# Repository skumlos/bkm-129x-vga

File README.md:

The BKM-129X compatible with VGA instead of BNC.

Including a sync combiner circuit to run with both CSYNC and HVSYNC. This circuit was made up
by Ste from HD Retrovision as far as I know.

Requires Arduino Nano v3.0 loaded with the software from https://github.com/skumlos/bkm-129x-mcu

Revision log:

B: Fixed THS7374 bypass and VGA pin 9 connectivity. Update to Kicad 5.

A: Initial revision

(2020) Martin Hejnfelt (martin@hejnfelt.com)

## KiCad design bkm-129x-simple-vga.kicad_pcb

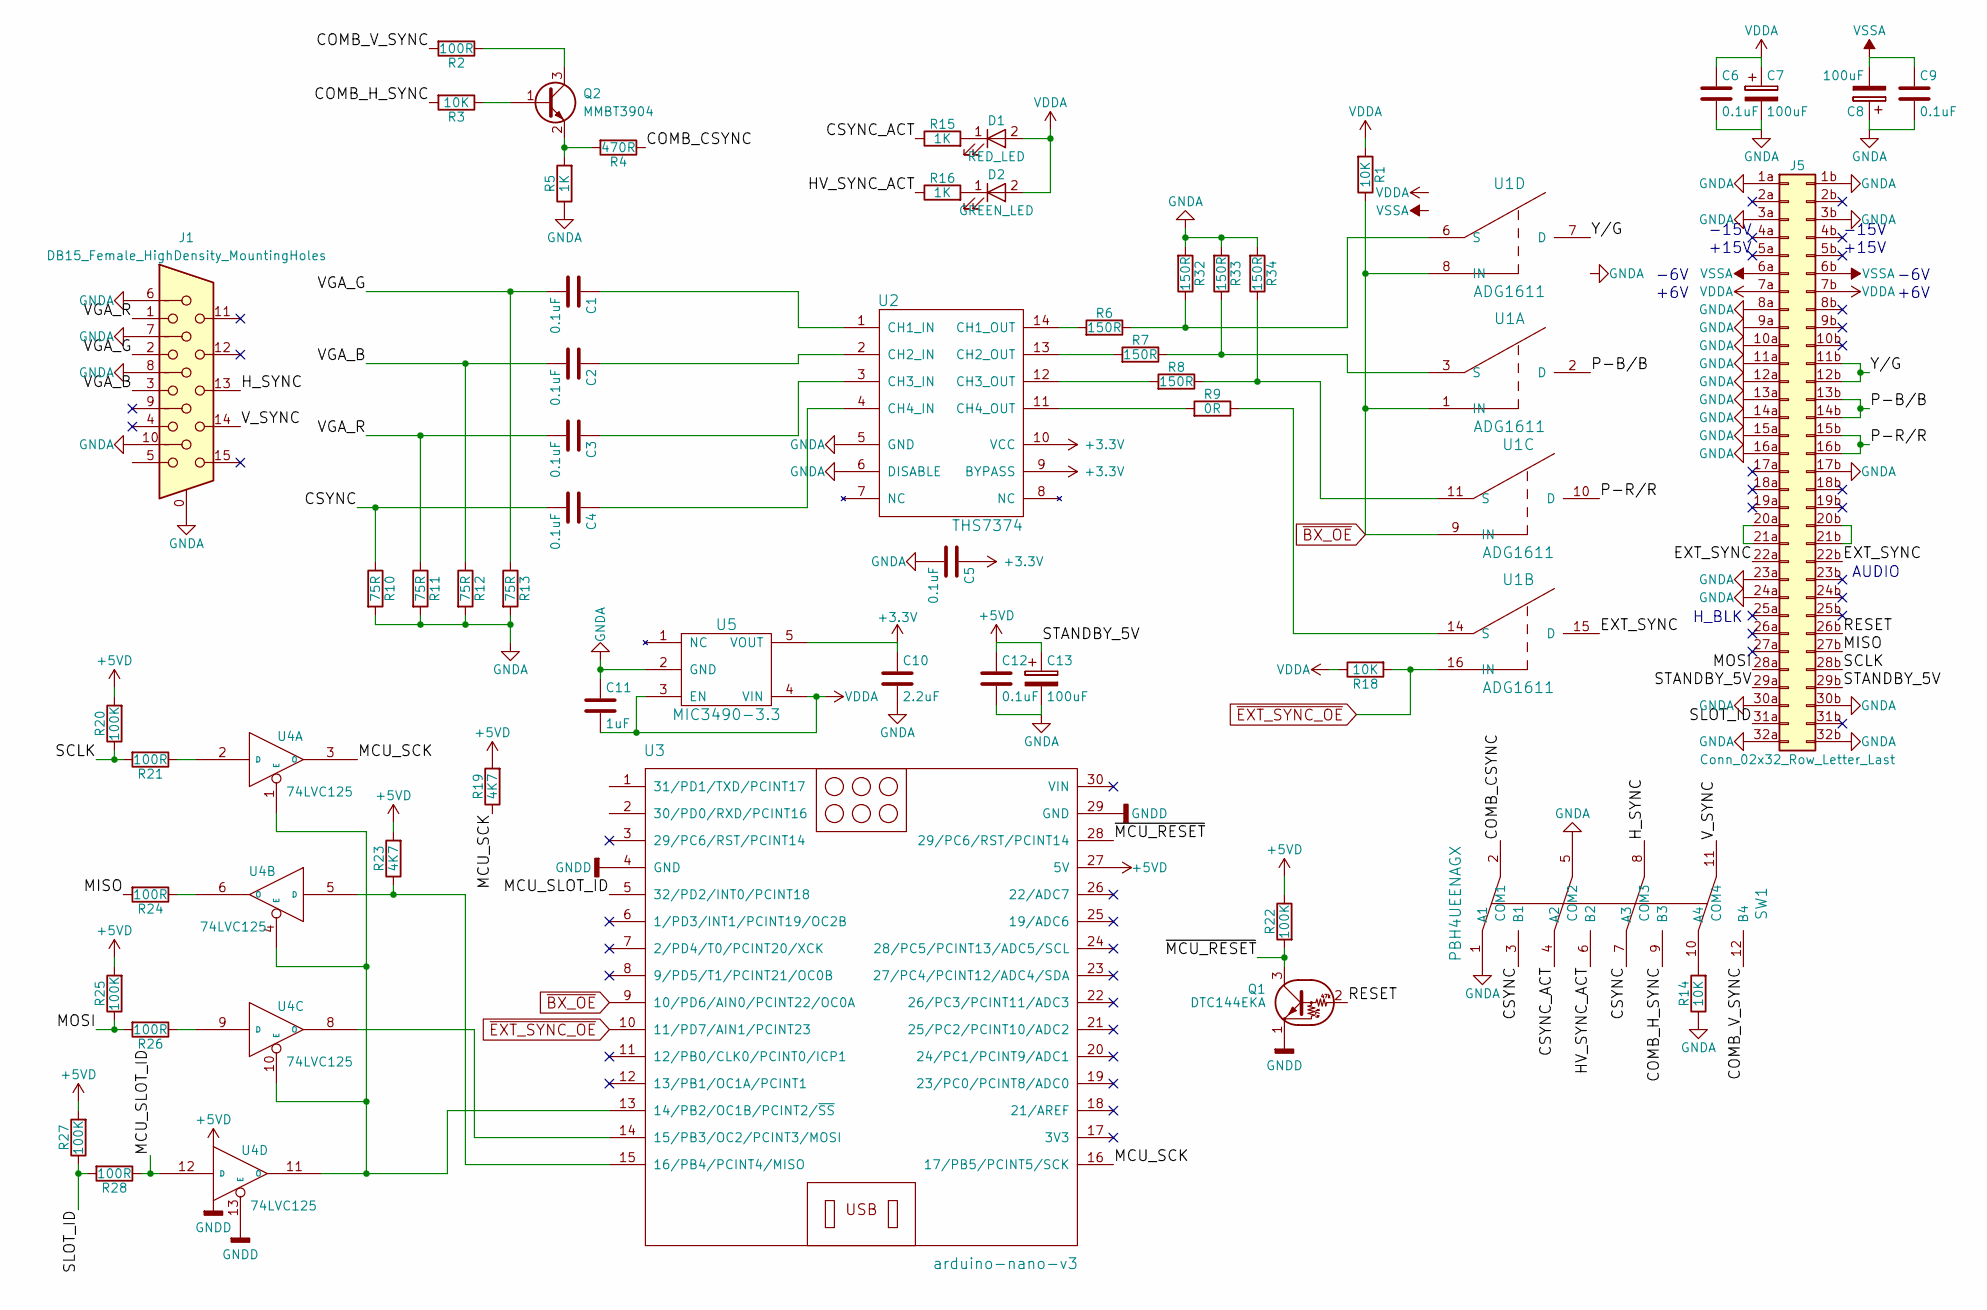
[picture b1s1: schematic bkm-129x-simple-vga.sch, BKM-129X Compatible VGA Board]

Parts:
C1, C2, C3, C4, C5, C6, C9, C12: 0.1uF; C_0805_HandSoldering
C7, C8, C13: 100uF; CP_Elec_6.3x5.3
C10: 2.2uF; C_0805_HandSoldering
C11: 1uF; C_0805_HandSoldering
D1: RED_LED; D_0805
D2: GREEN_LED; D_0805
J1: DB15_Female_HighDensity_MountingHoles; HD15-VGA
J5: Conn_02x32_Row_Letter_Last; DIN-41612-64P
Q1: DTC144EKA; SC-59_Handsoldering
Q2: MMBT3904; SOT-23_Handsoldering
R1, R3, R14, R18: 10K; R_0805_HandSoldering
R2, R21, R24, R26, R28: 100R; R_0805_HandSoldering
R4: 470R; R_0805_HandSoldering
R5, R15, R16: 1K; R_0805_HandSoldering
R6, R7, R8, R32, R33, R34: 150R; R_0805_HandSoldering
R9: 0R; R_0805_HandSoldering
R10, R11, R12, R13: 75R; R_0805_HandSoldering
R19, R23: 4K7; R_0805_HandSoldering
R20, R22, R25, R27: 100K; R_0805_HandSoldering
SW1: PBH4UEENAGX; PBH4UEE
U1: ADG1611; TSSOP-16_4.4x5mm_Pitch0.65mm
U2: THS7374; TSSOP-14_4.4x5mm_Pitch0.65mm
U3: arduino-nano-v3
U4: 74LVC125; TSSOP-14_4.4x5mm_Pitch0.65mm
U5: MIC3490-3.3; SOT-23-5_HandSoldering

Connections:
+3V3: C5.1, C10.1, U2.9 (BYPASS), U2.10 (VCC), U5.5 (VOUT)
+5VD: C12.1, C13.1, J5.29a, J5.29b, R19.2, R20.2, R22.1, R23.2, R25.2, R27.2, U3.27 (5V), U4.14 (VCC)
/COMB_CSYNC: R4.1, SW1.2 (COM1)
/COMB_H_SYNC: R3.2, SW1.9 (B3)
/COMB_V_SYNC: R2.2, SW1.12 (B4)
/CSYNC: C4.2, R10.1, SW1.3 (B1), SW1.7 (A3)
/CSYNC_ACT: R15.1, SW1.4 (A2)
/EXT_SYNC: J5.22a, J5.22b, U1.15 (D)
/HV_SYNC_ACT: R16.1, SW1.6 (B2)
/H_SYNC: J1.13, SW1.8 (COM3)
/MCU_SCK: R19.1, U3.16 (17/PB5/PCINT5/SCK), U4.3 (O)
/MCU_SLOT_ID: R28.1, U3.5 (32/PD2/INT0/PCINT18), U4.12 (D)
/MISO: J5.27b, R24.2
/MOSI: J5.28a, R25.1, R26.2
/P-B/B: J5.13b, J5.14b, U1.2 (D)
/P-R/R: J5.15b, J5.16b, U1.10 (D)
/RESET: J5.26b, Q1.2 (B)
/SCLK: J5.28b, R20.1, R21.2
/SLOT_ID: J5.31a, R27.1, R28.2
/VGA_B: C2.2, J1.3, R12.1
/VGA_G: C1.2, J1.2, R13.1
/VGA_R: C3.2, J1.1, R11.1
/V_SYNC: J1.14, SW1.11 (COM4)
/Y/G: J5.11b, J5.12b, U1.7 (D)
/~MCU_RESET: Q1.3 (C), R22.2, U3.28 (29/PC6/RST/PCINT14)
unnamed: C1.1, U2.1 (CH1_IN)
unnamed: C2.1, U2.2 (CH2_IN)
unnamed: C3.1, U2.3 (CH3_IN)
unnamed: C4.1, U2.4 (CH4_IN)
unnamed: D1.1 (K), R15.2
unnamed: D2.1 (K), R16.2
unnamed: J5.20a, J5.21a
unnamed: J5.20b, J5.21b
unnamed: Q2.1 (B), R3.1
unnamed: Q2.2 (E), R4.2, R5.2
unnamed: Q2.3 (C), R2.1
unnamed: R6.2, U2.14 (CH1_OUT)
unnamed: R7.2, U2.13 (CH2_OUT)
unnamed: R8.2, U2.12 (CH3_OUT)
unnamed: R9.1, U1.14 (S)
unnamed: R9.2, U2.11 (CH4_OUT)
unnamed: R14.2, SW1.10 (A4)
unnamed: R21.1, U4.2 (D)
unnamed: R23.1, U3.15 (16/PB4/PCINT4/MISO), U4.5 (D)
unnamed: R24.1, U4.6 (O)
unnamed: R26.1, U4.9 (D)
unnamed: R6.1, R32.1, U1.6 (S)
unnamed: R7.1, R33.1, U1.3 (S)
unnamed: R8.1, R34.1, U1.11 (S)
unnamed: U3.13 (14/PB2/OC1B/PCINT2/~SS), U4.1 (E), U4.4 (E), U4.10 (E), U4.11 (O)
unnamed: U3.14 (15/PB3/OC2/PCINT3/MOSI), U4.8 (O)
VDD: C6.1, C7.1, C11.2, D1.2 (A), D2.2 (A), J5.7a, J5.7b, R1.2, R18.1, U1.13 (VDD), U5.3 (EN), U5.4 (VIN)
VSS: C8.2, C9.1, J5.6a, J5.6b, U1.4 (VSS)
~BX_OE: R1.1, U1.1 (IN), U1.8 (IN), U1.9 (IN), U3.9 (10/PD6/AIN0/PCINT22/OC0A)
~EXT_SYNC_OE: R18.2, U1.16 (IN), U3.10 (11/PD7/AIN1/PCINT23)

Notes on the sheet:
-15V
+15V
-6V
+6V
AUDIO
H_BLK

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
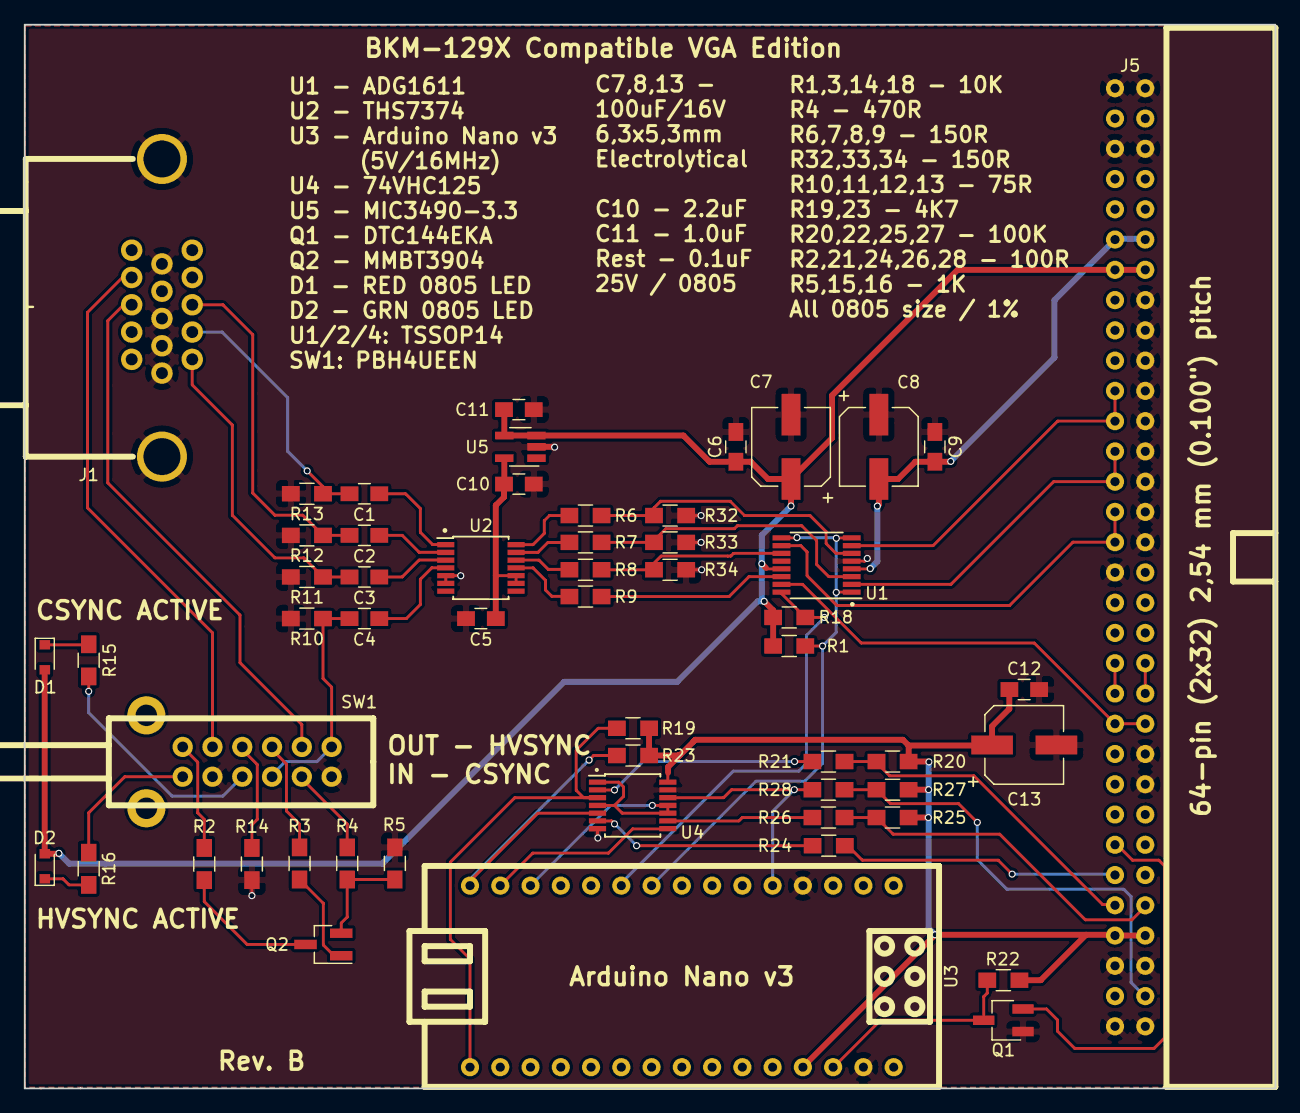
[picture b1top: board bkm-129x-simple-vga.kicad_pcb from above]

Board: 2 copper layers, 105.0 x 89.3 mm, 55 parts (0 on the bottom side), 56 nets.

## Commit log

2021-05-09 Rev. B: Fix THS7374, VGA pin 9, Kicad 5
2021-05-09 Added some missing Kicad files
